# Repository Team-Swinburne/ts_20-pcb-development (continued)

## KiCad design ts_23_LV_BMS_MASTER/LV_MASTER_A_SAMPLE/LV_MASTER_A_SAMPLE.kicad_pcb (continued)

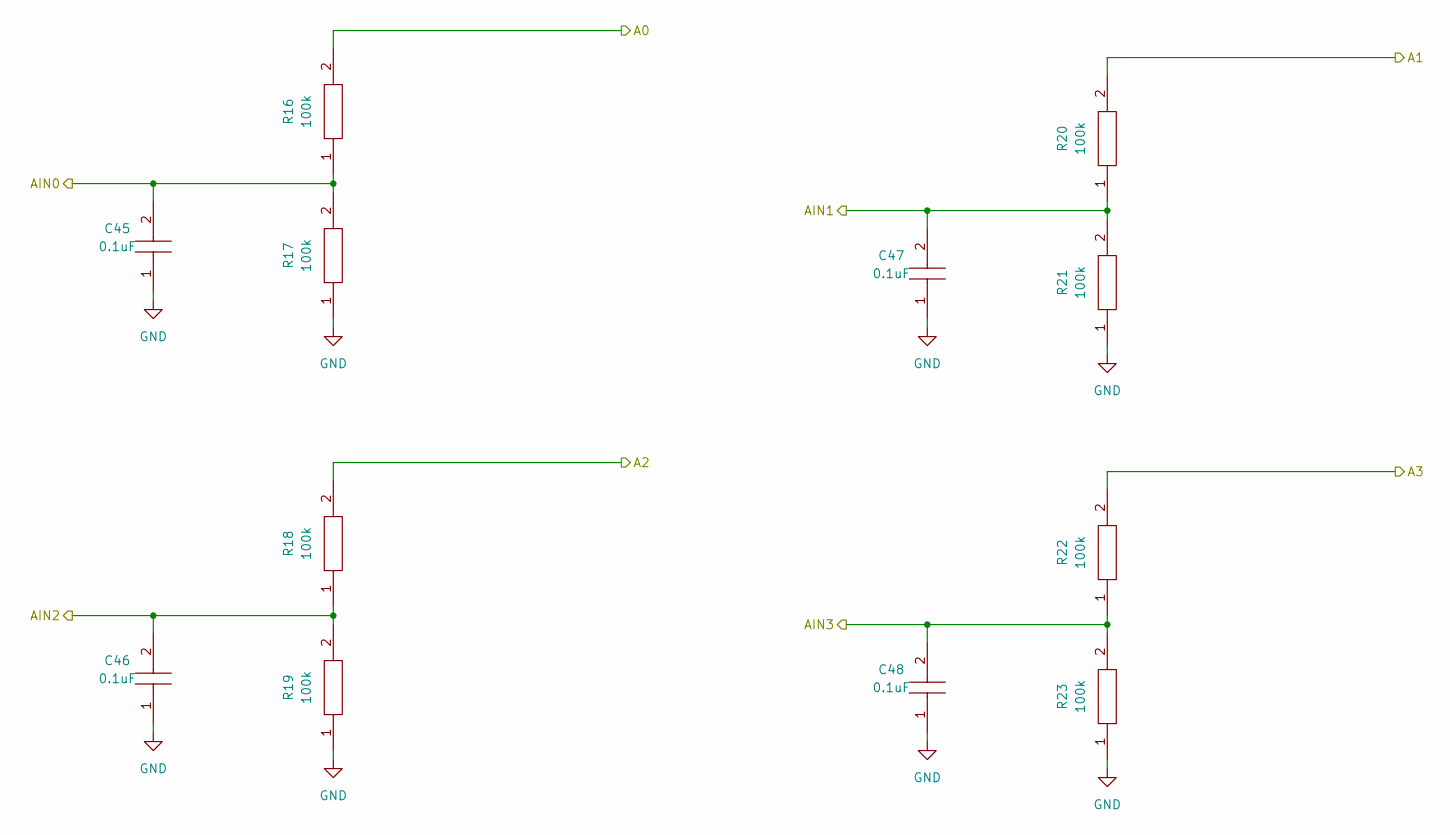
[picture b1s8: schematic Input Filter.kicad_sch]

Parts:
C45, C46, C47, C48: 0.1uF; C_0603_1608Metric_Pad1.08x0.95mm_HandSolder; Manufacturer_Part_Number CC0805JRX7R8BB104; Mouser Part Number 603-CC805JRX7R8BB104
R16, R17, R18, R19, R20, R21, R22, R23: 100k; R_0603_1608Metric_Pad0.98x0.95mm_HandSolder; Manufacturer_Part_Number ERJP06F1000V

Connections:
/CS1A: R16.2; also elsewhere on the board
/CS1B: R20.2; also elsewhere on the board
/CS2A: R18.2; also elsewhere on the board
/CS2B: R22.2; also elsewhere on the board
/Current Sense/Input Filter/AIN0: C45.2, R16.1, R17.2; also elsewhere on the board
/Current Sense/Input Filter/AIN1: C47.2, R20.1, R21.2; also elsewhere on the board
/Current Sense/Input Filter/AIN2: C46.2, R18.1, R19.2; also elsewhere on the board
/Current Sense/Input Filter/AIN3: C48.2, R22.1, R23.2; also elsewhere on the board

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
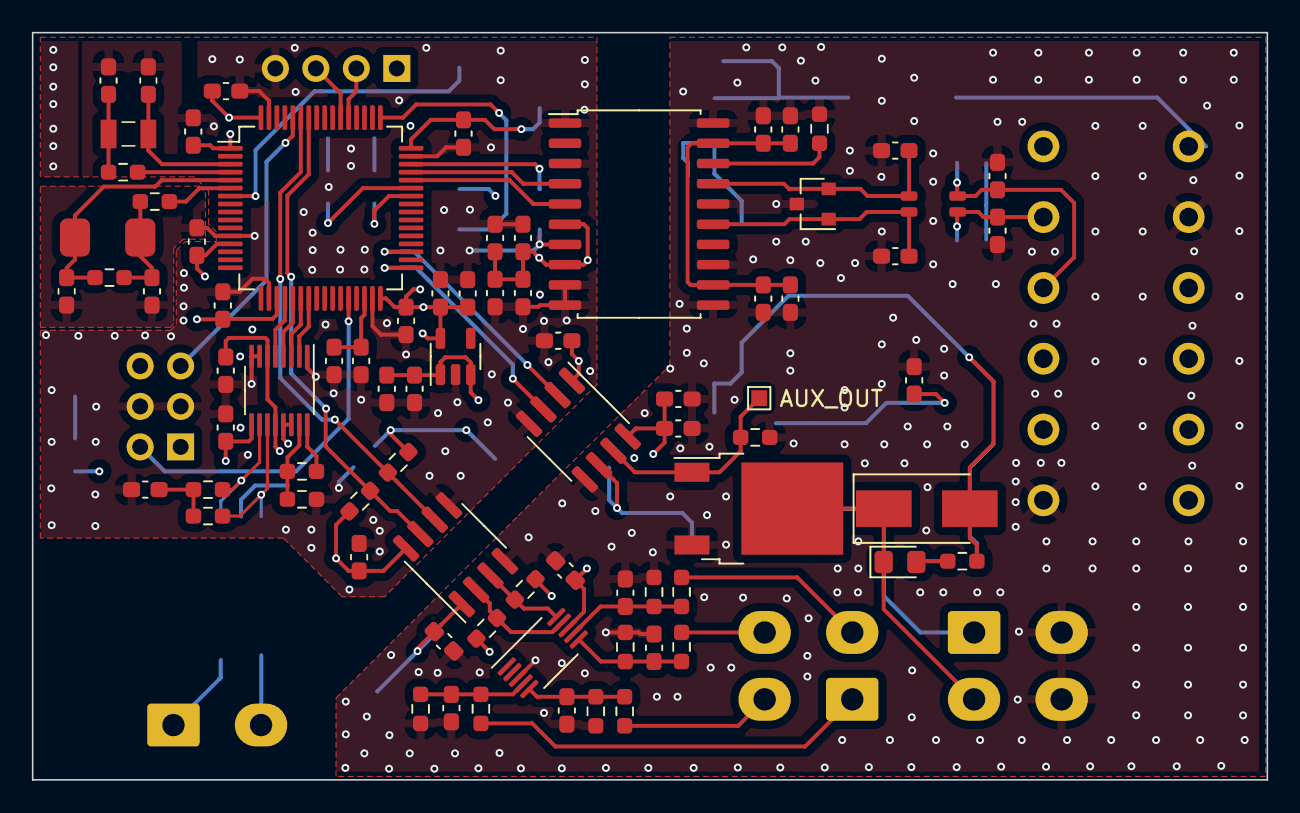
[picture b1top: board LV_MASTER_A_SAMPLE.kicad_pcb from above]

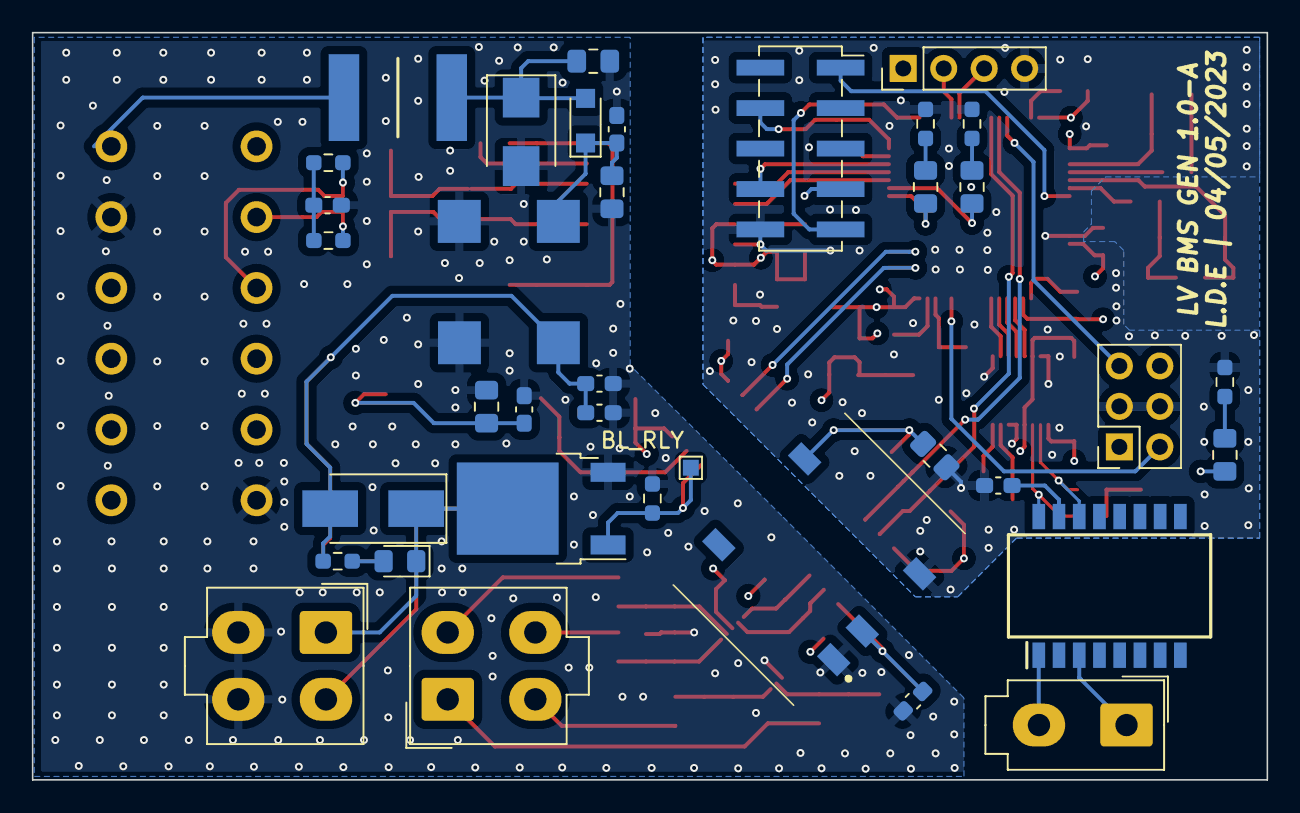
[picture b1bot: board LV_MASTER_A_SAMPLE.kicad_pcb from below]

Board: 4 copper layers, 77.5 x 46.9 mm, 117 parts (37 on the bottom side), 69 nets.

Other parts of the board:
AUX_OUT: AUX_OUT; TestPoint_Pad_1.0x1.0mm
BL_RLY: BL_RLY; TestPoint_Pad_1.0x1.0mm
R29: 50mR; R_0603_1608Metric_Pad0.98x0.95mm_HandSolder

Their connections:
/Blue Loop/VOA: AUX_OUT.1; also elsewhere on the board
/Blue Loop/VOB: BL_RLY.1; also elsewhere on the board
/Microcontroller/XTAL32_OUT: R29.2; also elsewhere on the board
unnamed 52: R29.1; also elsewhere on the board

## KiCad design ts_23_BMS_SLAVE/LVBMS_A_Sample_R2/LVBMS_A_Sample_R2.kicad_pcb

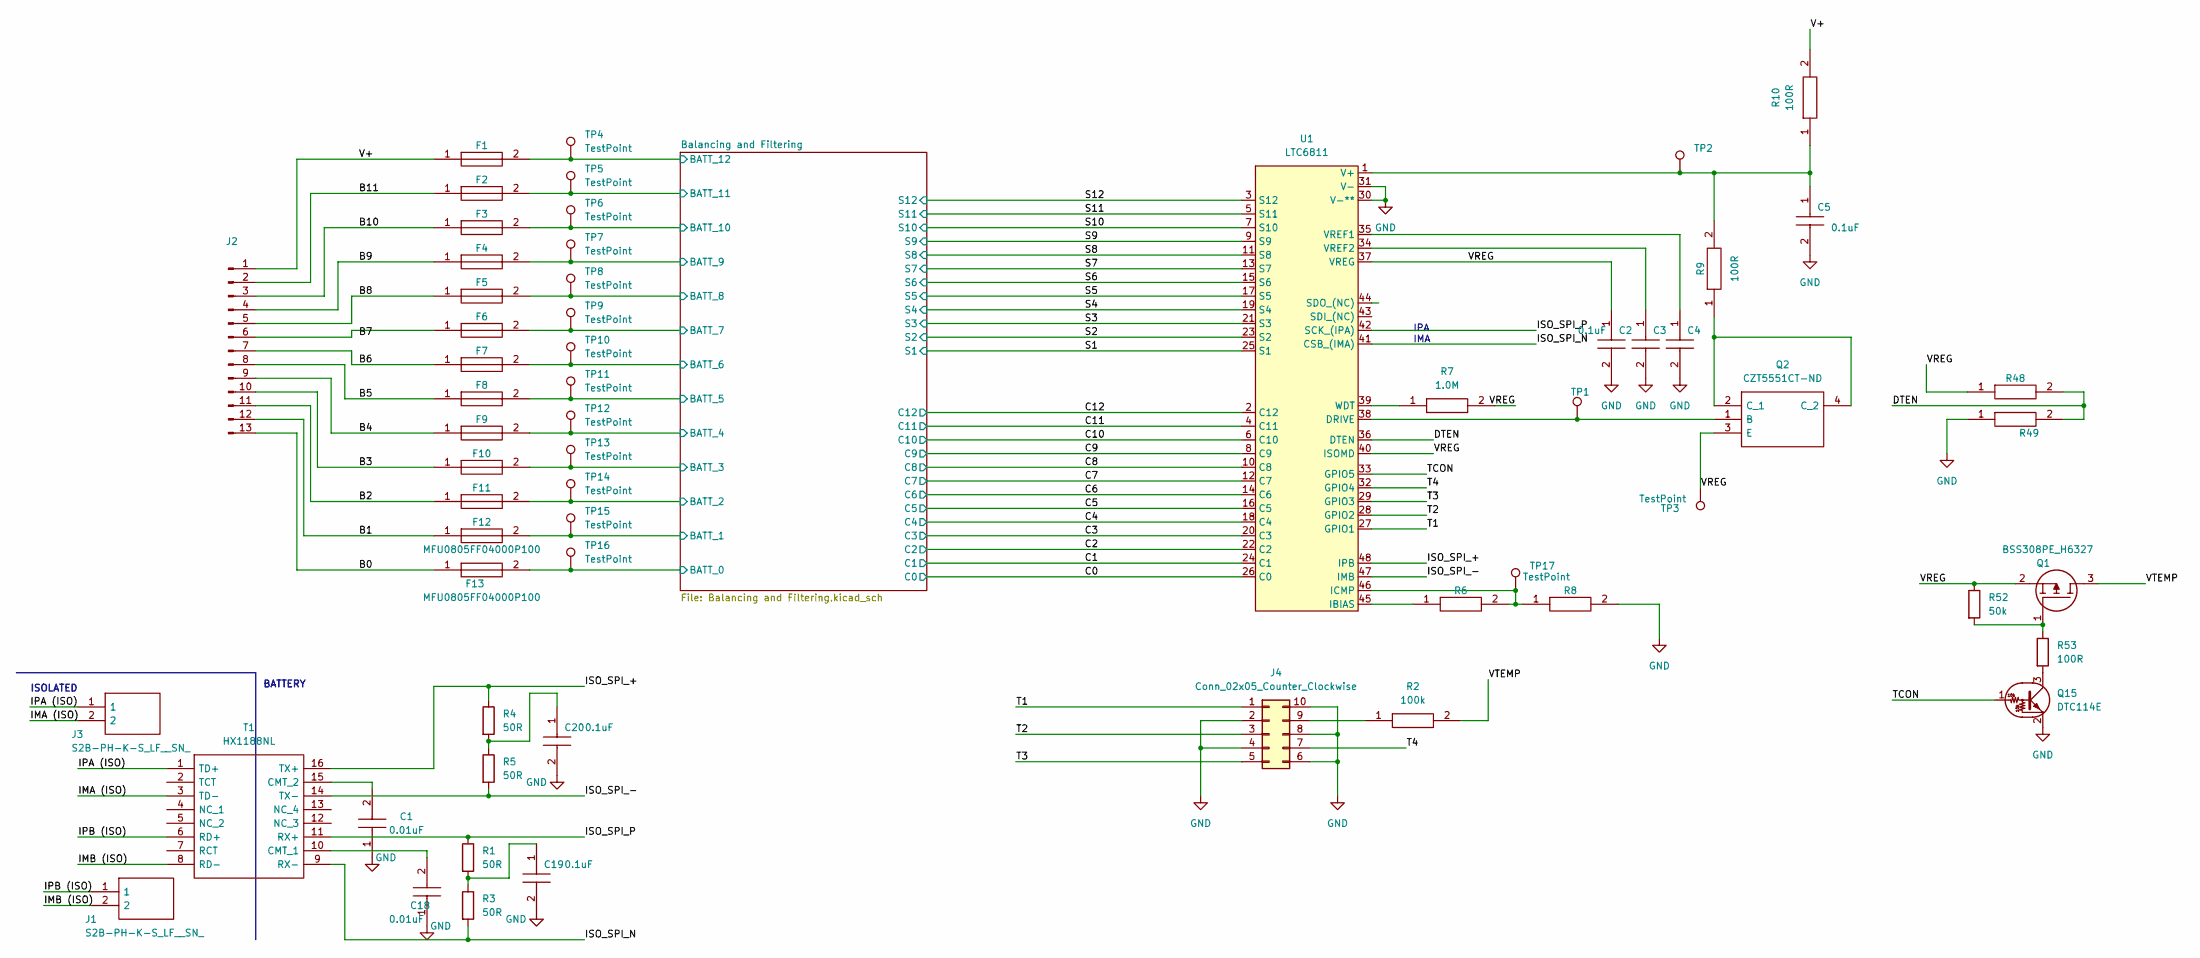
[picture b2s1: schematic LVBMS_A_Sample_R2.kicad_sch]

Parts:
C1, C18: 0.01uF; C_0603_1608Metric_Pad1.08x0.95mm_HandSolder; Manufacturer_Part_Number CC0805JRX7R9BB103
C2, C3, C4, C5, C19, C20: 0.1uF; C_0603_1608Metric_Pad1.08x0.95mm_HandSolder; Manufacturer_Part_Number CC0805JRX7R8BB104; Mouser Part Number 603-CC805JRX7R8BB104
F1, F2, F3, F4, F5, F6, F7, F8, F9, F10, F11, F12, F13: MFU0805FF04000P100; Fuse_0603_1608Metric_Pad1.05x0.95mm_HandSolder; Manufacturer_Part_Number MFU0805FF04000P100; Mouser Part Number 594-MFU0805FF04000P1
J1, J3: S2B-PH-K-S_LF__SN_; Molex_Mini-Fit_Jr_5566-02A_2x01_P4.20mm_Vertical; Manufacturer_Part_Number S2B-PH-K-S(LF)(SN)
J2: Conn_01x13_Male; PinSocket_1x13_P2.54mm_Vertical
J4: Conn_02x05_Counter_Clockwise; PinSocket_2x05_P2.54mm_Vertical
Q1: BSS308PE_H6327; SOT95P260X110-3N; Manufacturer_Part_Number BSS308PE H6327; Mouser Part Number 726-BSS308PEH6327
Q2: CZT5551CT-ND; SOT230P700X180-4N; Manufacturer_Part_Number CZT5551CT-ND
Q15: DTC114E; SOT-23
R1, R3, R4, R5: 50R; R_0603_1608Metric_Pad0.98x0.95mm_HandSolder
R2: 100k; R_0603_1608Metric_Pad0.98x0.95mm_HandSolder; Manufacturer_Part_Number ERJP06F1000V
R6: BIAS RESISTOR (VALUE CHANGES); R_0603_1608Metric_Pad0.98x0.95mm_HandSolder; Manufacturer_Part_Number ERJP06F1000V
R7: 1.0M; R_0603_1608Metric_Pad0.98x0.95mm_HandSolder; Manufacturer_Part_Number ERJ-P06J105V; Mouser Part Number 667-ERJ-P06J105V
R8: BIAS RESISTOR (VALUE CAN CHANGE); R_0603_1608Metric_Pad0.98x0.95mm_HandSolder; Manufacturer_Part_Number ERJP06F1000V
R9, R10, R48, R49: 100R; R_0603_1608Metric_Pad0.98x0.95mm_HandSolder; Manufacturer_Part_Number ERJP06F1000V
R52: 50k; R_0603_1608Metric_Pad0.98x0.95mm_HandSolder
R53: 100R; R_0603_1608Metric_Pad0.98x0.95mm_HandSolder
T1: HX1188NL; SOIC127P940X597-16N; Manufacturer_Part_Number HX1188NL; Mouser Part Number 673-HX1188NL
TP1, TP2, TP3, TP4, TP5, TP6, TP7, TP8, TP9, TP10, TP11, TP12, TP13, TP14, TP15, TP16, TP17: TestPoint; TestPoint_Pad_D1.0mm
U1: LTC6811

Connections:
/B0: F13.1, J2.13
/B1: F12.1, J2.12
/B2: F11.1, J2.11
/B3: F10.1, J2.10
/B4: F9.1, J2.9
/B5: F8.1, J2.8
/B6: F7.1, J2.7
/B8: F5.1, J2.5
/B9: F4.1, J2.4
/B10: F3.1, J2.3
/B11: F2.1, J2.2
/Balancing and Filtering/BATT_0: F13.2, TP16.1; also elsewhere on the board
/Balancing and Filtering/BATT_1: F12.2, TP15.1; also elsewhere on the board
/Balancing and Filtering/BATT_2: F11.2, TP14.1; also elsewhere on the board
/Balancing and Filtering/BATT_3: F10.2, TP13.1; also elsewhere on the board
/Balancing and Filtering/BATT_4: F9.2, TP12.1; also elsewhere on the board
/Balancing and Filtering/BATT_5: F8.2, TP11.1; also elsewhere on the board
/Balancing and Filtering/BATT_6: F7.2, TP10.1; also elsewhere on the board
/Balancing and Filtering/BATT_7: F6.2, TP9.1; also elsewhere on the board
/Balancing and Filtering/BATT_8: F5.2, TP8.1; also elsewhere on the board
/Balancing and Filtering/BATT_9: F4.2, TP7.1; also elsewhere on the board
/Balancing and Filtering/BATT_10: F3.2, TP6.1; also elsewhere on the board
/Balancing and Filtering/BATT_11: F2.2, TP5.1; also elsewhere on the board
/Balancing and Filtering/BATT_12: F1.2, TP4.1; also elsewhere on the board
/C1: U1.24 (C1); also elsewhere on the board
/C2: U1.22 (C2); also elsewhere on the board
/C3: U1.20 (C3); also elsewhere on the board
/C4: U1.18 (C4); also elsewhere on the board
/C5: U1.16 (C5); also elsewhere on the board
/C6: U1.14 (C6); also elsewhere on the board
/C7: U1.12 (C7); also elsewhere on the board
/C8: U1.10 (C8); also elsewhere on the board
/C9: U1.8 (C9); also elsewhere on the board
/C10: U1.6 (C10); also elsewhere on the board
/C11: U1.4 (C11); also elsewhere on the board
/C12: U1.2 (C12); also elsewhere on the board
/DTEN: R48.2, R49.2, U1.36 (DTEN)
/IMA (ISO): J3.2, T1.3 (TD-)
/IMB (ISO): J1.2, T1.8 (RD-)
/IPA (ISO): J3.1, T1.1 (TD+)
/IPB (ISO): J1.1, T1.6 (RD+)
/ISO_SPI_+: R4.1, T1.16 (TX+), U1.48 (IPB)
/ISO_SPI_-: R5.2, T1.14 (TX-), U1.47 (IMB)
/ISO_SPI_N: R3.2, T1.9 (RX-), U1.41 (CSB_(IMA))
/ISO_SPI_P: R1.1, T1.11 (RX+), U1.42 (SCK_(IPA))
/S1: U1.25 (S1); also elsewhere on the board
/S2: U1.23 (S2); also elsewhere on the board
/S3: U1.21 (S3); also elsewhere on the board
/S4: U1.19 (S4); also elsewhere on the board
/S5: U1.17 (S5); also elsewhere on the board
/S6: U1.15 (S6); also elsewhere on the board
/S7: U1.13 (S7); also elsewhere on the board
/S8: U1.11 (S8); also elsewhere on the board
/S9: U1.9 (S9); also elsewhere on the board
/S10: U1.7 (S10); also elsewhere on the board
/S11: U1.5 (S11); also elsewhere on the board
/S12: U1.3 (S12); also elsewhere on the board
/T1: J4.1, U1.27 (GPIO1)
/T2: J4.3, U1.28 (GPIO2)
/T3: J4.5, U1.29 (GPIO3)
/T4: J4.7, U1.32 (GPIO4)
/TCON: Q15.1 (B), U1.33 (GPIO5)
/V+: F1.1, J2.1, R10.2
/VREG: C2.1, Q1.2, Q2.3 (E), R7.2, R48.1, R52.1, TP3.1, U1.37 (VREG), U1.40 (ISOMD)
/VTEMP: Q1.3, R2.2
GND: C1.1, C2.2, C3.2, C4.2, C5.2, C18.1, C19.2, C20.2, J4.2, J4.4, J4.6, J4.8, J4.10, Q15.2 (E), R8.2, R49.1, U1.26 (C0), U1.30 (V-**), U1.31 (V-); also elsewhere on the board
unnamed: C1.2, T1.15 (CMT_2)
unnamed: C3.1, U1.34 (VREF2)
unnamed: C4.1, U1.35 (VREF1)
unnamed: C5.1, R9.2, R10.1, TP2.1, U1.1 (V+)
unnamed: C19.1, R1.2, R3.1
unnamed: C20.1, R4.2, R5.1
unnamed: F6.1, J2.6
unnamed: J4.9, R2.1
unnamed: Q1.1, R52.2, R53.1
unnamed: Q2.1 (B), TP1.1, U1.38 (DRIVE)
unnamed: Q2.2 (C_1), Q2.4 (C_2), R9.1
unnamed: Q15.3 (C), R53.2
unnamed: R7.1, U1.39 (WDT)
unnamed: C18.2, T1.10 (CMT_1)
unnamed: R6.1, U1.45 (IBIAS)
unnamed: R6.2, R8.1, TP17.1, U1.46 (ICMP)

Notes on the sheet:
IPA IMA
BATTERY
ISOLATED

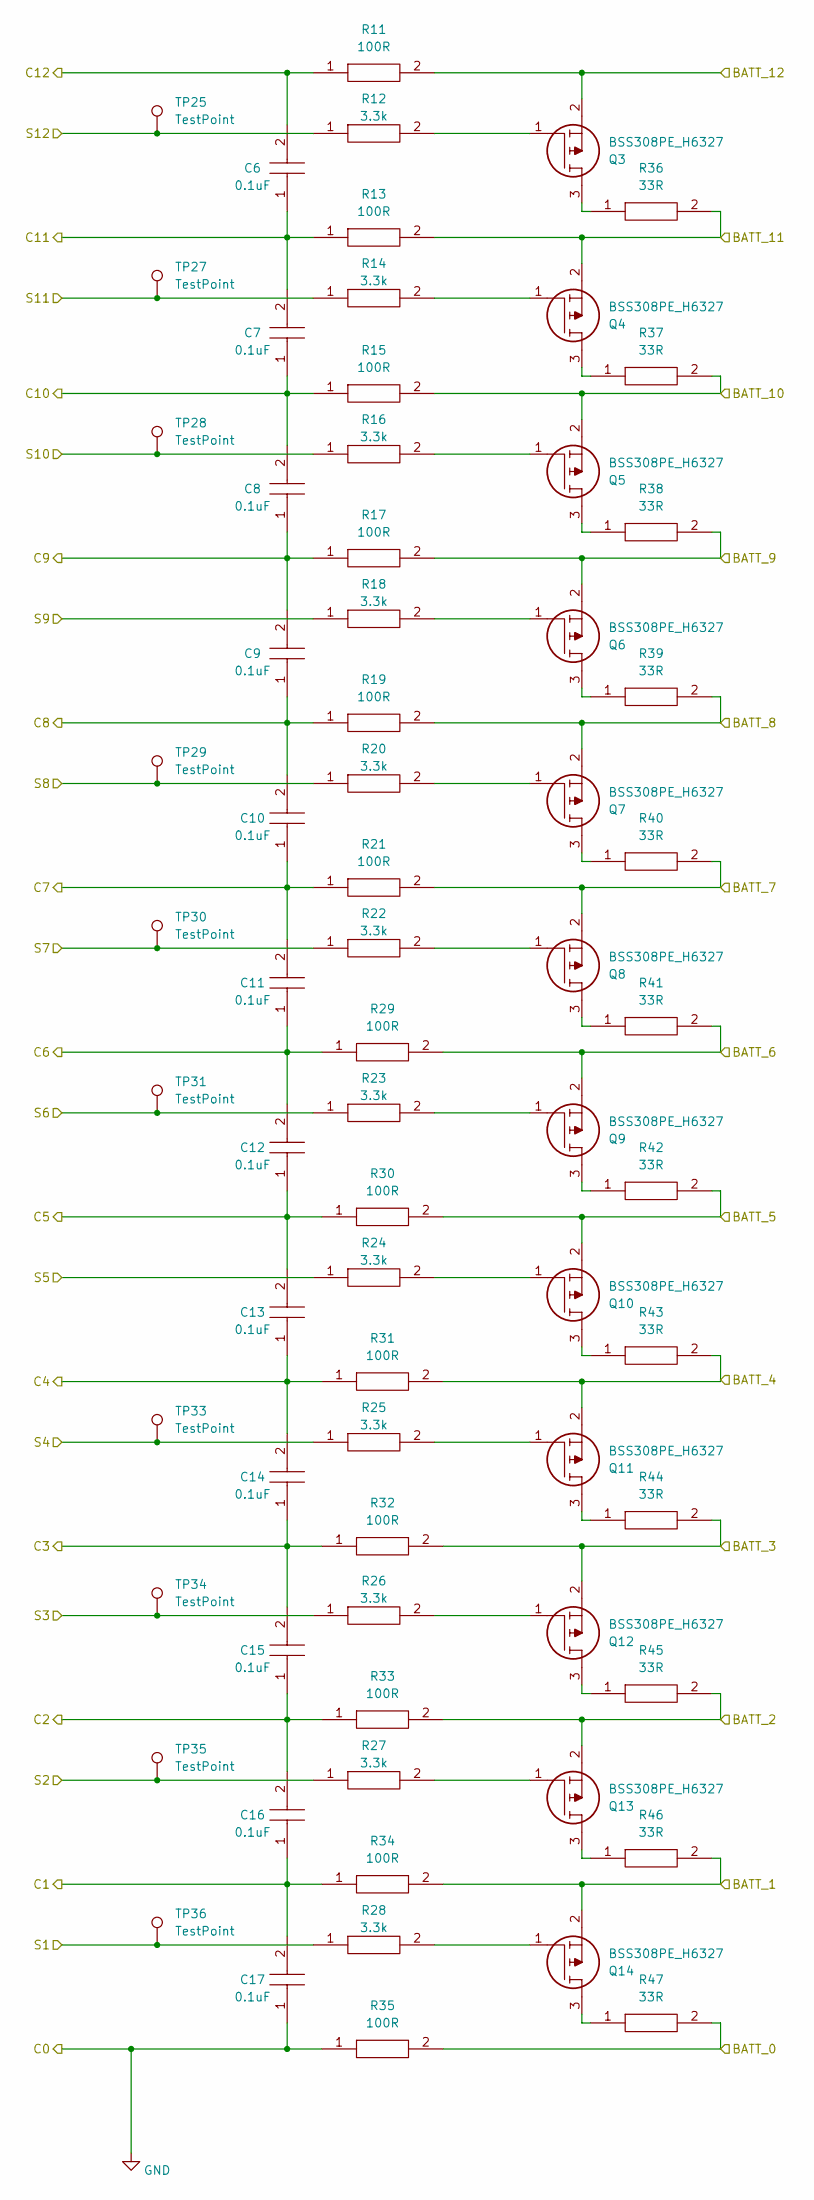
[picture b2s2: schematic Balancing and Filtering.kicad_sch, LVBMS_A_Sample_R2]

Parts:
C6, C7, C8, C9, C10, C11, C12, C13, C14, C15, C16, C17: 0.1uF; C_0603_1608Metric_Pad1.08x0.95mm_HandSolder; Manufacturer_Part_Number CC0805JRX7R9BB103
Q3, Q4, Q5, Q6, Q7, Q8, Q9, Q10, Q11, Q12, Q13, Q14: BSS308PE_H6327; SOT95P260X110-3N; Manufacturer_Part_Number BSS308PE H6327; Mouser Part Number 726-BSS308PEH6327
R11, R13, R15, R17, R19, R21, R29, R30, R31, R32, R33, R34, R35: 100R; R_0603_1608Metric_Pad0.98x0.95mm_HandSolder; Manufacturer_Part_Number ERJP06F1000V
R12, R14, R16, R18, R20, R22, R23, R24, R25, R26, R27, R28: 3.3k; R_0603_1608Metric_Pad0.98x0.95mm_HandSolder; Manufacturer_Part_Number ERJP06J332V
R36, R37, R38, R39, R40, R41, R42, R43, R44, R45, R46, R47: 33R; R_1206_3216Metric_Pad1.30x1.75mm_HandSolder; Manufacturer_Part_Number ERJ-P6WF33R0V; Mouser Part Number 667-ERJ-P6WF33R0V
TP25, TP27, TP28, TP29, TP30, TP31, TP33, TP34, TP35, TP36: TestPoint; TestPoint_Pad_D1.0mm

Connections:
/Balancing and Filtering/BATT_0: R35.2, R47.2; also elsewhere on the board
/Balancing and Filtering/BATT_1: Q14.2, R34.2, R46.2; also elsewhere on the board
/Balancing and Filtering/BATT_2: Q13.2, R33.2, R45.2; also elsewhere on the board
/Balancing and Filtering/BATT_3: Q12.2, R32.2, R44.2; also elsewhere on the board
/Balancing and Filtering/BATT_4: Q11.2, R31.2, R43.2; also elsewhere on the board
/Balancing and Filtering/BATT_5: Q10.2, R30.2, R42.2; also elsewhere on the board
/Balancing and Filtering/BATT_6: Q9.2, R29.2, R41.2; also elsewhere on the board
/Balancing and Filtering/BATT_7: Q8.2, R21.2, R40.2; also elsewhere on the board
/Balancing and Filtering/BATT_8: Q7.2, R19.2, R39.2; also elsewhere on the board
/Balancing and Filtering/BATT_9: Q6.2, R17.2, R38.2; also elsewhere on the board
/Balancing and Filtering/BATT_10: Q5.2, R15.2, R37.2; also elsewhere on the board
/Balancing and Filtering/BATT_11: Q4.2, R13.2, R36.2; also elsewhere on the board
/Balancing and Filtering/BATT_12: Q3.2, R11.2; also elsewhere on the board
/C1: C16.1, C17.2, R34.1; also elsewhere on the board
/C2: C15.1, C16.2, R33.1; also elsewhere on the board
/C3: C14.1, C15.2, R32.1; also elsewhere on the board
/C4: C13.1, C14.2, R31.1; also elsewhere on the board
/C5: C12.1, C13.2, R30.1; also elsewhere on the board
/C6: C11.1, C12.2, R29.1; also elsewhere on the board
/C7: C10.1, C11.2, R21.1; also elsewhere on the board
/C8: C9.1, C10.2, R19.1; also elsewhere on the board
/C9: C8.1, C9.2, R17.1; also elsewhere on the board
/C10: C7.1, C8.2, R15.1; also elsewhere on the board
/C11: C6.1, C7.2, R13.1; also elsewhere on the board
/C12: C6.2, R11.1; also elsewhere on the board
/S1: R28.1, TP36.1; also elsewhere on the board
/S2: R27.1, TP35.1; also elsewhere on the board
/S3: R26.1, TP34.1; also elsewhere on the board
/S4: R25.1, TP33.1; also elsewhere on the board
/S5: R24.1; also elsewhere on the board
/S6: R23.1, TP31.1; also elsewhere on the board
/S7: R22.1, TP30.1; also elsewhere on the board
/S8: R20.1, TP29.1; also elsewhere on the board
/S9: R18.1; also elsewhere on the board
/S10: R16.1, TP28.1; also elsewhere on the board
/S11: R14.1, TP27.1; also elsewhere on the board
/S12: R12.1, TP25.1; also elsewhere on the board
GND: C17.1, R35.1; also elsewhere on the board
unnamed: Q3.1, R12.2
unnamed: Q3.3, R36.1
unnamed: Q4.1, R14.2
unnamed: Q4.3, R37.1
unnamed: Q5.1, R16.2
unnamed: Q5.3, R38.1
unnamed: Q6.1, R18.2
unnamed: Q6.3, R39.1
unnamed: Q7.1, R20.2
unnamed: Q7.3, R40.1
unnamed: Q8.1, R22.2
unnamed: Q8.3, R41.1
unnamed: Q9.1, R23.2
unnamed: Q9.3, R42.1
unnamed: Q10.1, R24.2
unnamed: Q10.3, R43.1
unnamed: Q11.1, R25.2
unnamed: Q11.3, R44.1
unnamed: Q12.1, R26.2
unnamed: Q12.3, R45.1
unnamed: Q13.1, R27.2
unnamed: Q13.3, R46.1
unnamed: Q14.1, R28.2
unnamed: Q14.3, R47.1

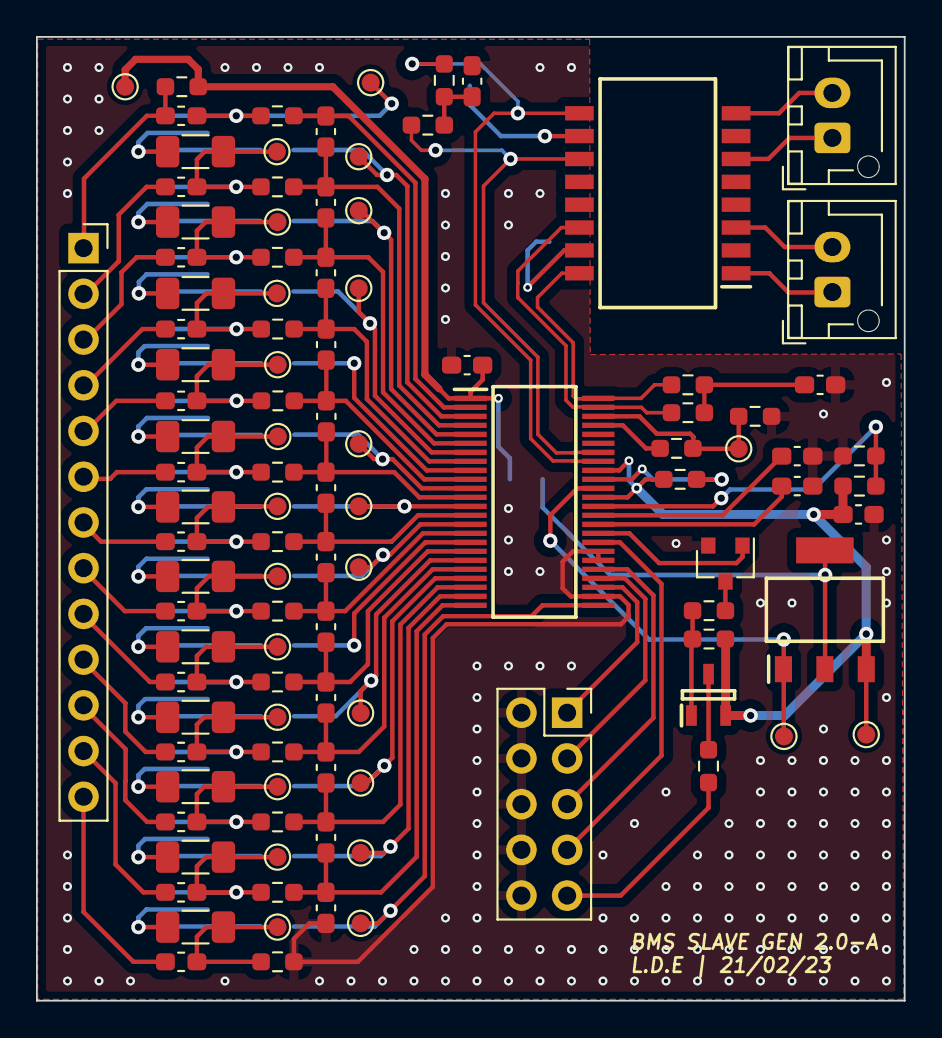
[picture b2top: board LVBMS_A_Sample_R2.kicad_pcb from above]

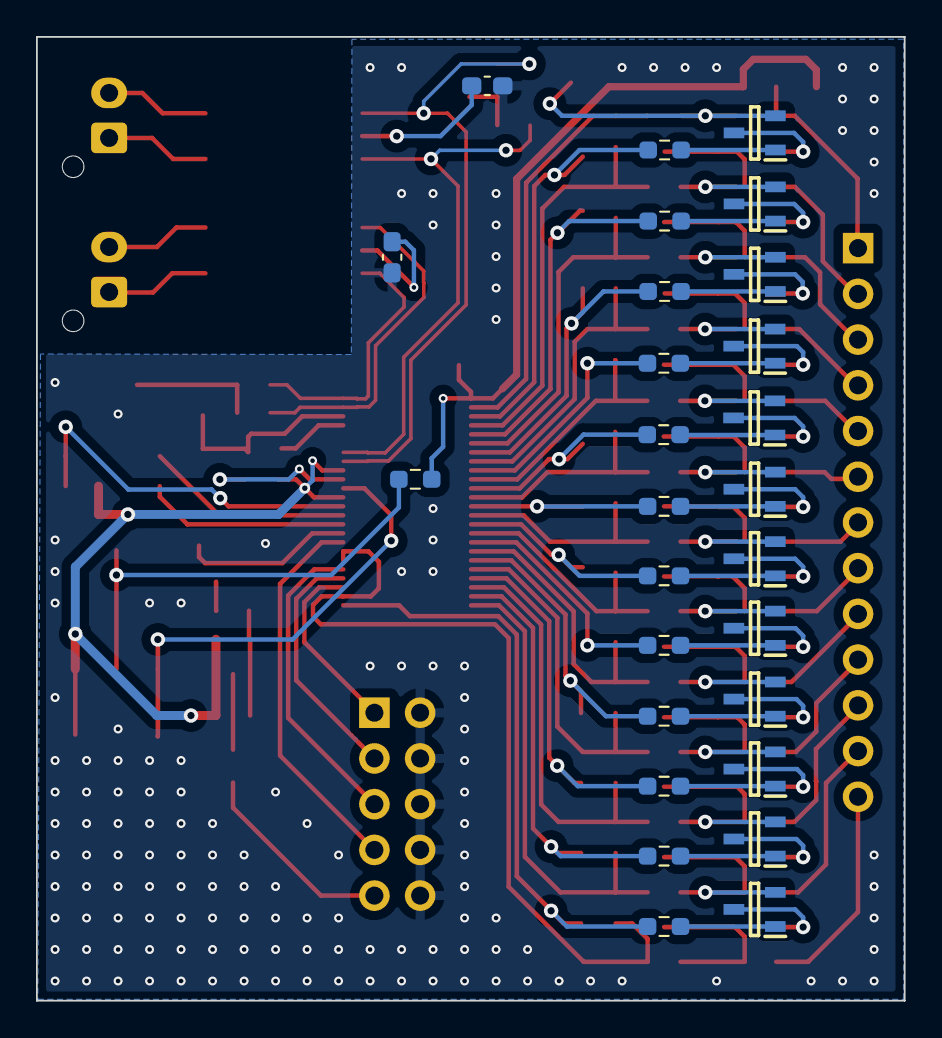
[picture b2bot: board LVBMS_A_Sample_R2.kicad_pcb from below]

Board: 2 copper layers, 48.2 x 53.5 mm, 132 parts (27 on the bottom side), 106 nets.

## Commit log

2019-12-22 Added template for 2020 temperature sensor
2019-12-29 Advancement in schematic for temperature sensor
2019-12-30 Updated PCB layout for temperature sensors
2020-01-05 Started work on brake module for ts_20 24V architecture
2020-01-06 Advanced schematic for Brake Module, still needs safety loops to be added
2020-01-08 Schematic at 50% for discharge module and additional changes to circuits to match them
2020-01-17 dicharge and temp board routing
2020-02-02 New revision of ts_20 precharge controller
2020-02-07 Smaller sense resistors for HV
2020-02-10 Modified Precharge Controller
2020-02-12 Added power calculations for discharge and precharge
2020-02-15 additional changes to the brake module
2020-02-15 Hardcore routing of ts_20 precharge newwwwwwwww
2020-02-17 More precharge modifications
2020-02-19 Completed precharge PCB routing awaiting approval
2020-02-20 Added precharge stuff
2020-02-20 updated part number for capacitor
2020-02-21 Updated version of UCM, 2020 edition, a modern classic
2020-02-21 Added review copy and line notes for precharge controller
2020-02-21 Added Review
2020-02-23 230220
2020-02-24 Orion Header Added
2020-02-24 Terminal Board Revision
2020-02-25 precharge controller changes
2020-02-27 Updated library with 556 timer
2020-02-27 New components and modifications to discharge and precharge
2020-02-27 New Brake Module Revision
2020-02-27 added HALO transformer
2020-02-27 added 556 in library database
2020-02-28 Brake Module Update
2020-02-28 added ltc6820 and began routing discharge
2020-02-29 Added license
2020-03-01 Terminal Board
2020-03-01 STarted routing UCM
2020-03-01 DTF13
2020-03-01 Partial UCM routing
2020-03-01 Connector Header
2020-03-01 UCM Routing
2020-03-02 Accumulator active indicator
2020-03-02 Added R6015ENJTL to library
2020-03-02 Routed Accumulator Active Light
2020-03-02 Add files via upload
    Manually Uploading Brake Module ~enjoy
2020-03-02 Add files via upload
    Formatted Updates
2020-03-03 Further Brake Module folder formating
2020-03-04 Additional routing to discharge module
2020-03-04 Merge
2020-03-05 Brake Module R2 update
2020-03-06 Final revision of Discharge with 5kW (R1)
2020-03-06 Added the damn header for the 10th time
2020-03-06 Hey ben, i've figured out why the header isn't getting added. In Windows, if a file is active, it is not able to be written to, so when Altium is open, it's using the excel file, and as such, cannot 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
2020-03-06 Brake Module Schematic Update
2020-03-07 Brake Module Update R1+R2
2020-03-07 Brake Module PCB update
2020-03-09 Discharge in 80% state
2020-03-09 Progress on revised AAI
2020-03-09 Brake Module Routing
2020-03-10 Added header to library
2020-03-10 New Brake Module verison and PCB update
2020-03-11 Added the pig
2020-03-12 Re-adding up to date project
2020-03-12 Changed board colour
2020-03-12 Finito
2020-03-12 Actually really maybe done now
2020-03-12 More precharging
2020-03-12 Added LTV847 bois
2020-03-12 Added SLDPRT
2020-03-12 Finished routing R3 Brake Module
2020-03-13 Brake Module R3 PCB
2020-03-15 Rerouted precharge R3, awaiting final part
2020-03-16 Changed footprints, completed precharge controller R3
2020-03-17 Added new HV logo and additional finalisations for precharge controller
2020-03-17 Added new resistor to lib
2020-03-17 Added DTF13 4PA plug
2020-03-17 New Revision
2020-03-18 minor correction
2020-03-18 new caps
2020-03-18 more new caps
2020-03-18 Library Update
2020-03-18 Completed discharge
2020-03-18 Rules for discharge updated
2020-03-19 Moved LED for Ben
2020-03-19 New components, and finalisation of PI CAN interface
2020-03-20 Minor cahnges to manufacturing
2020-03-24 Precharge changes
2020-03-25 Added R3-1 review for Precharge Controller
2020-03-25 MOre minor changes
2020-03-26 discharge
2020-03-26 Added Review R3-2 for precharge controller
2020-03-26 slight modification, trying out how to use altium's version manager
2020-03-27 Approaching ready for manufacturing for precharge and discharge PCBs
2020-03-28 Terminal Board Routing
2020-03-29 no message
2020-03-29 Final Discharge Design Before Manufacturing
2020-03-29 Completed PI CAN Interface, release for manufacturing
2020-03-29 same thing
2020-03-29 Final revisions for precharge, discharge, and rpi
2020-03-31 Terminal board R2
2020-03-31 Just kidding, this is R2
2020-03-31 Fixed molex library
2020-03-31 Completed routing on terminal pcb
2020-03-31 Routed terminal board R2
2020-04-03 HV Clearence
2020-04-03 UCM Folder Structure
2020-04-03 UCM update
2020-04-04 Brake Module Sync
2020-04-04 Brake Module R4 Update
2020-04-04 More changes to the header library and precharge controller additional stuff for notes
2020-04-04 AAI Clean Up
2020-04-04 Brake Module Aesthetics
2020-04-11 Small updates for readabliity
2020-04-11 Added OP07D and Small Diode
2020-04-11 Touch Up
2020-04-11 Test Points Added
2020-04-11 i've gone nuts
2020-04-12 UCM Microcontroller Update
2020-04-12 Continued UCM Routing (13-04-20)
2020-04-14 Rules Check
2020-04-14 Folder Clean Up
2020-04-15 trace width
2020-04-16 Updated UCMPCB
2020-04-16 Ben i love you, but for the love of god, stop breaking Git
2020-04-17 Brake Module Touch Up
2020-04-18 UCM Update 18/04/20
2020-04-20 UCM update 20/04/20
2020-04-21 Refined emergency current detector PCB for manufacturing
2020-04-21 Minor schematic adjustment
2020-04-22 556 re-added to library
2020-04-26 UCM update R0-R1
2020-04-26 pdf's
2020-04-28 ucm r1 UPDATE
2020-04-28 Created TSAL
    Hello World
2020-04-28 Update_excel_database
2020-04-28 UCM Board
2020-04-29 UCM R1 Fixed
2020-04-29 UCM R1 with Polygon Pour
2020-04-29 UCM R1 Final
2020-04-30 Disco Dash
2020-04-30 UCM Fix
2020-04-30 Final UCM
2020-04-30 Terminal Board UCM, fixes
2020-05-03 UCM Antonio Fixes
2020-05-04 UCM pour fixes
2020-05-04 Fixed UCM 4-05-20
2020-05-04 UCM fixes 5-05-20
2020-05-05 Footprint Fixs
2020-05-05 Fixed UCM
2020-05-05 Final UCM Antonio Tick of approval
2020-05-06 Final touch up?
2020-05-06 Added simulation of input filter for design report
2020-05-06 Pat's requested touch up
2020-05-07 Wave 2
2020-05-08 analog mistake
2020-05-09 Library Update and footprint fixes
2020-05-09 footprint
2020-05-09 Added missing footprint
2020-05-10 Disco Fix
2020-05-17 Schematic draft without calculation
2020-05-17 New components, FTDI programmer, and MAX6755
2020-05-17 First Calculation
2020-05-19 New Screwy bois
2020-05-22 Reflow oven schematic :
2020-06-02 Here's a gift Ben and Tom, plug the IMU into anywhere, Love Patrick
2020-06-05 A little present
2020-07-26 Completed calculation
2020-08-08 Changes to reflow oven/dischrage. Minor revisions for assisting readability
2020-08-09 Add mounting holde _ TS Lable
2020-08-15 Added bench test loom designs
2020-08-16 Trolly discharge - added full trace
2020-08-19 Trolly Discharge R2 with better clearance
2020-08-22 More little notes for the little mistakes we make along the way :)
2020-08-23 Added stm32f446 to library & adjusted 3.3V regulator symbol
2020-08-23 Started arranging CB
2020-08-25 Minor changes to test F446 sample schematic
2020-08-25 Missed can2 tx
2020-08-27 Drill table + more labels
2020-08-27 Switching to GLV for relay on Trolly Discharge
2020-08-31 Update resistor values in Trolly Discharge
2020-09-17 DTM Connectors
2020-09-27 Added signal registry for precharge
2020-10-17 Added some pots
2020-11-11 Added some library stuff
2020-12-29 Telemetry Unit pcb
2020-12-30 Fix Footpath not found on some connectors
2021-03-19 Add TS_20 Disco Dash
2021-03-21 Some discharge preview stuff, should be in the .gitignore
2021-03-25 Fix for UCM (Jumper wires. Still Needs PWM Pins and replaced Digital IC)
2021-03-25 Add R0 to TS_20 Dash
2021-04-21 Update surface.pcb
    Added footprint for 6-pin RGB LED to surface library - M. Walters.
2021-04-22 Current Sensor Changes
2021-05-04 Fix PWM Pins on UCM
2021-05-24 Add 2 CUI DC-DC Converter
2021-05-28 Added some discharge and precharge stuff
2021-06-20 Added new Corner Board prototype
2021-06-26 added some precharge stuff and changed database references
2021-06-26 Added 16Mhz smd crystal
2021-06-28 Changes made to break module to fix jumper leads. (Needs to be checked by Nam or Ben).
2021-07-07 Brake Module Fixes (Needs to be check by Ben)
2021-07-25 Preparing to add components
2021-07-25 Added bulk capacitors and input TVS
2021-07-28 Pre library upate push
2021-07-28 Added H Bridge
2021-07-30 Added new i2c adc
2021-09-16 Corner board updates
2021-09-18 Updated precharge to r4, rerouted HV section
2021-09-22 Added composite oven controller project
2021-09-22 Added BOM
2021-09-25 Routed Precharge GLV section and added JST xh
2021-09-29 Steering Wheel Board Updates
2021-09-29 minor changes
2021-09-29 Uploads
2021-09-29 Zipped
2021-09-29 Zipped Files
2021-09-29 Zipped Charger
2021-09-29 Autonomous terminal board
2021-10-02 Begung adding larger planes
2021-10-22 routed out leds and some other paths, still need to change over crystal
2021-10-24 Some Changes for sourceman
2021-10-24 Hopefully cutout works
2021-10-28 Brake Light
2021-10-29 Completed routing, entering refinement stages
2021-12-21 Finished routing precharging, refining final features
2021-12-22 Revision changes
2022-01-02 Refinement notes from TB, thnak you
2022-01-08 Precharge ready for manufacturing
2022-01-09 precharge r4b sent to pcbway
2022-05-20 stuff
2023-02-08 .zip in git ignore
2023-02-08 Deleting .zip files
2023-02-08 Teensy Added to component library
2023-02-08 modified .gitignore to inlcude desktop.ini
2023-02-08 Deleted all useless desktop.ini files lol
2023-05-04 PCB Development Q1 2023
2023-05-04 Changes to Fabrication Table
2023-05-09 LV_BMS PCB Uploads
2023-06-25 Latest Updates for 23 development
2023-09-20 Changes to Brake Module
